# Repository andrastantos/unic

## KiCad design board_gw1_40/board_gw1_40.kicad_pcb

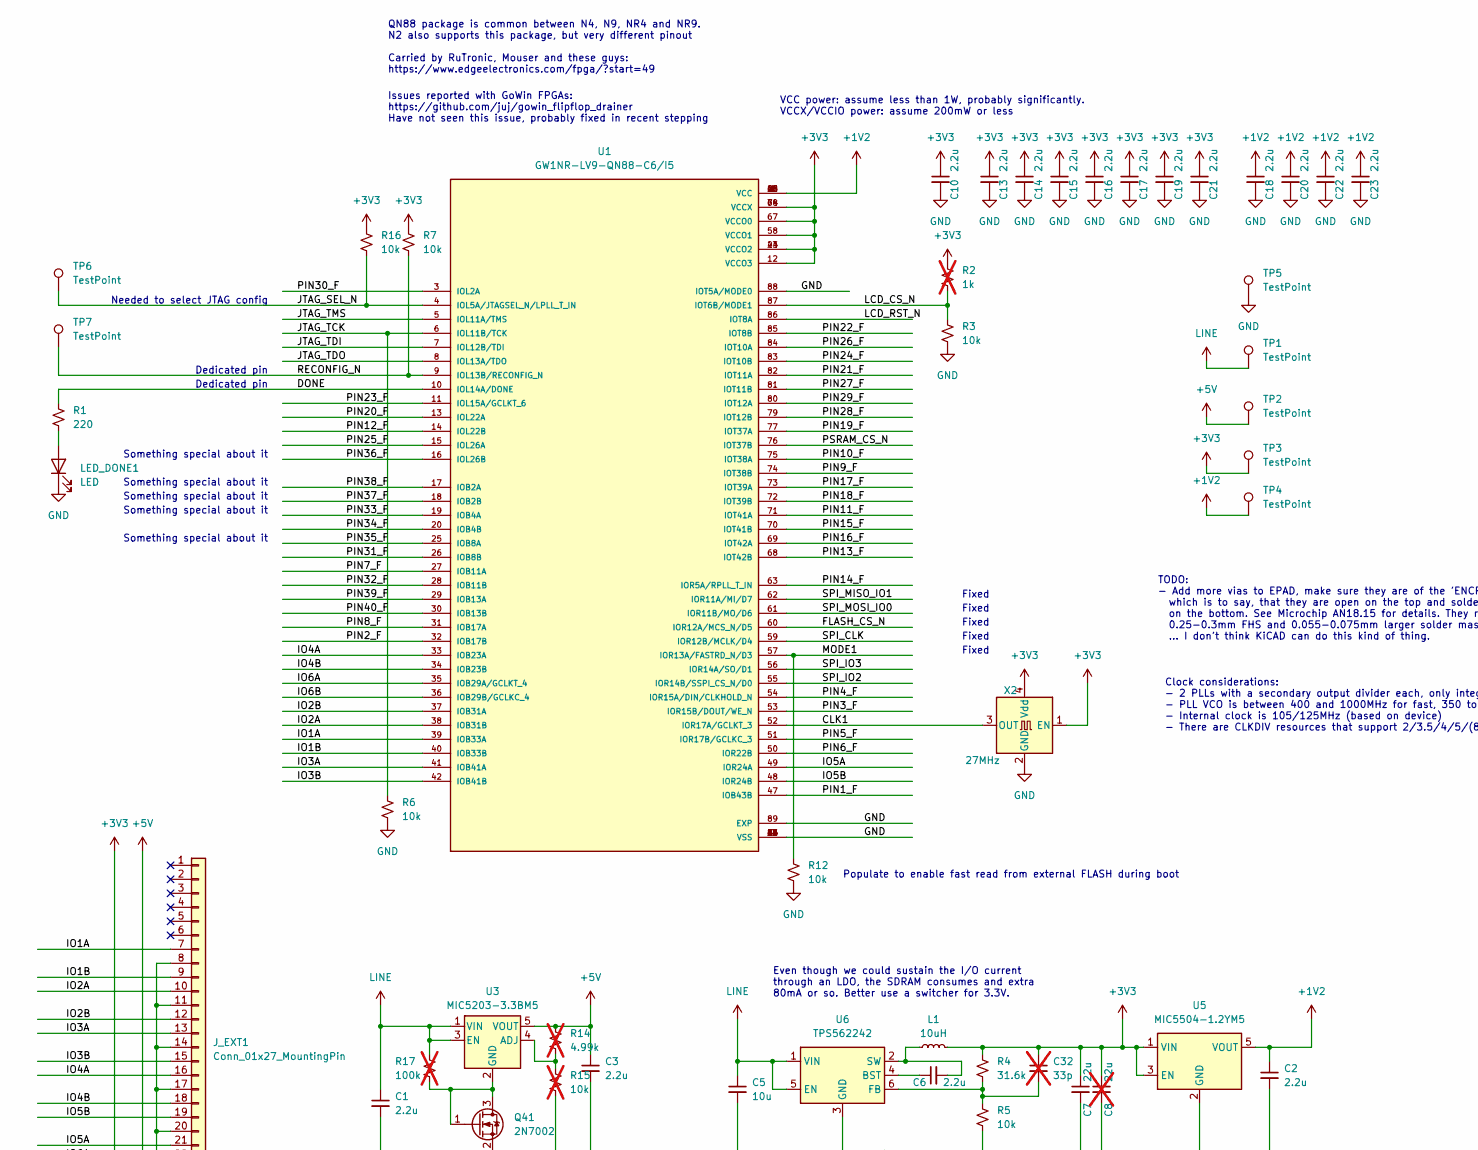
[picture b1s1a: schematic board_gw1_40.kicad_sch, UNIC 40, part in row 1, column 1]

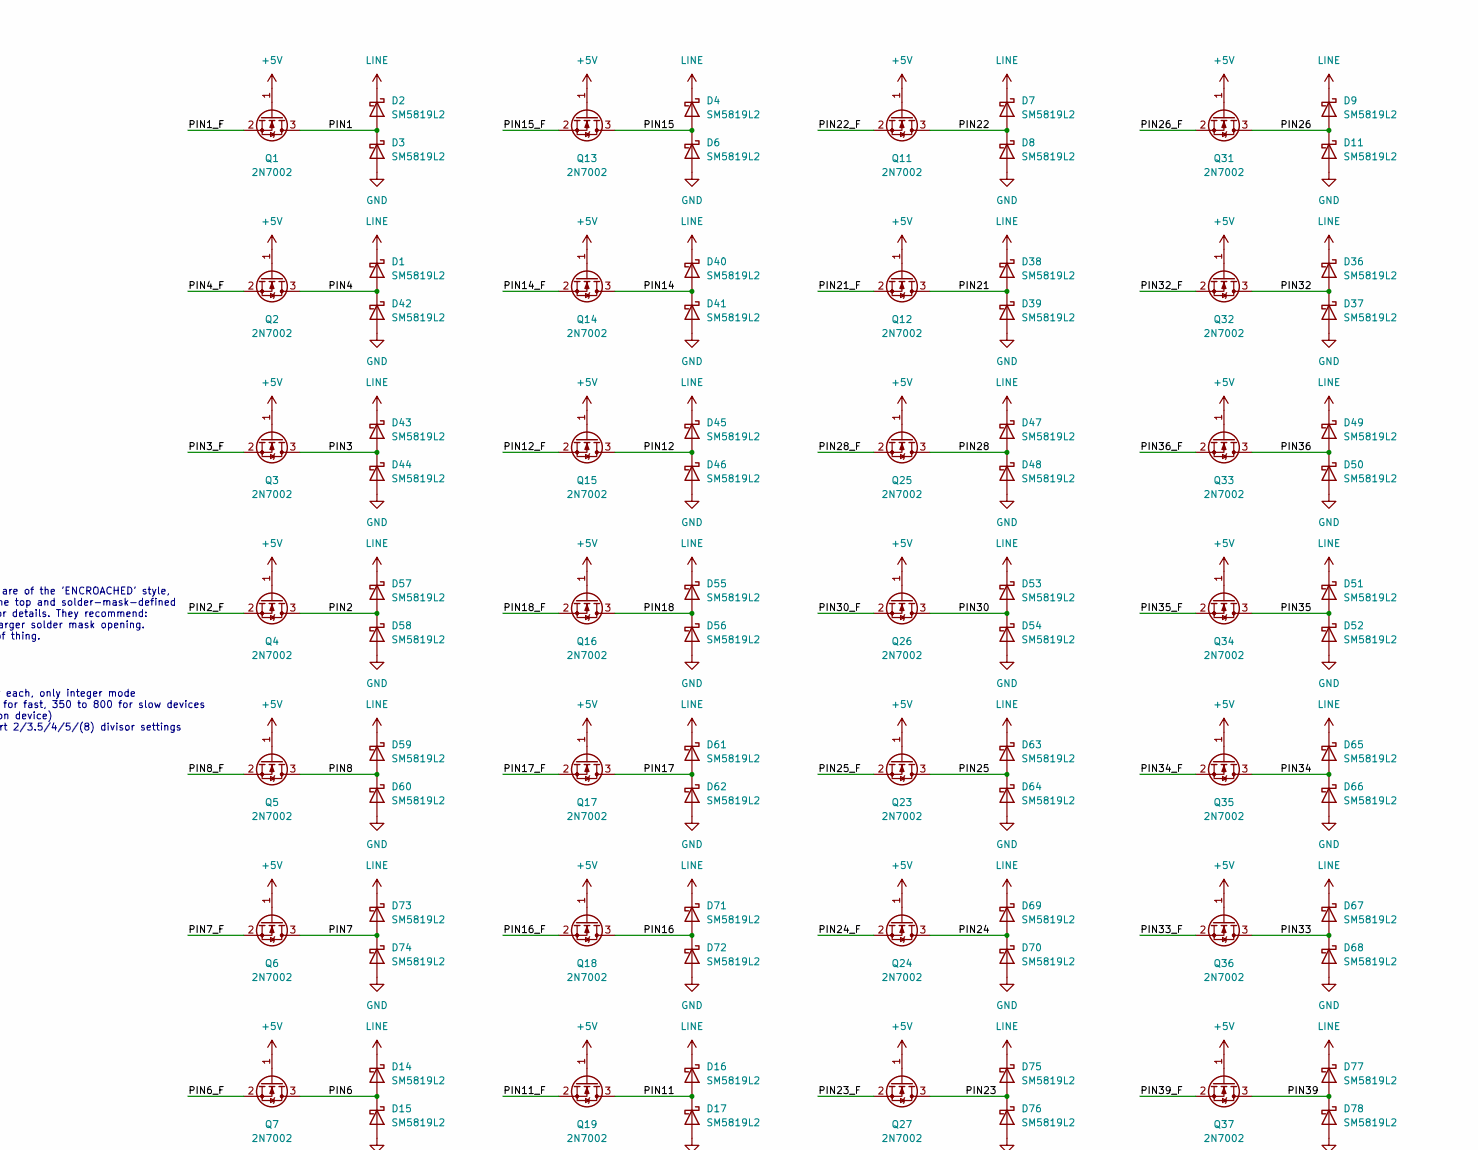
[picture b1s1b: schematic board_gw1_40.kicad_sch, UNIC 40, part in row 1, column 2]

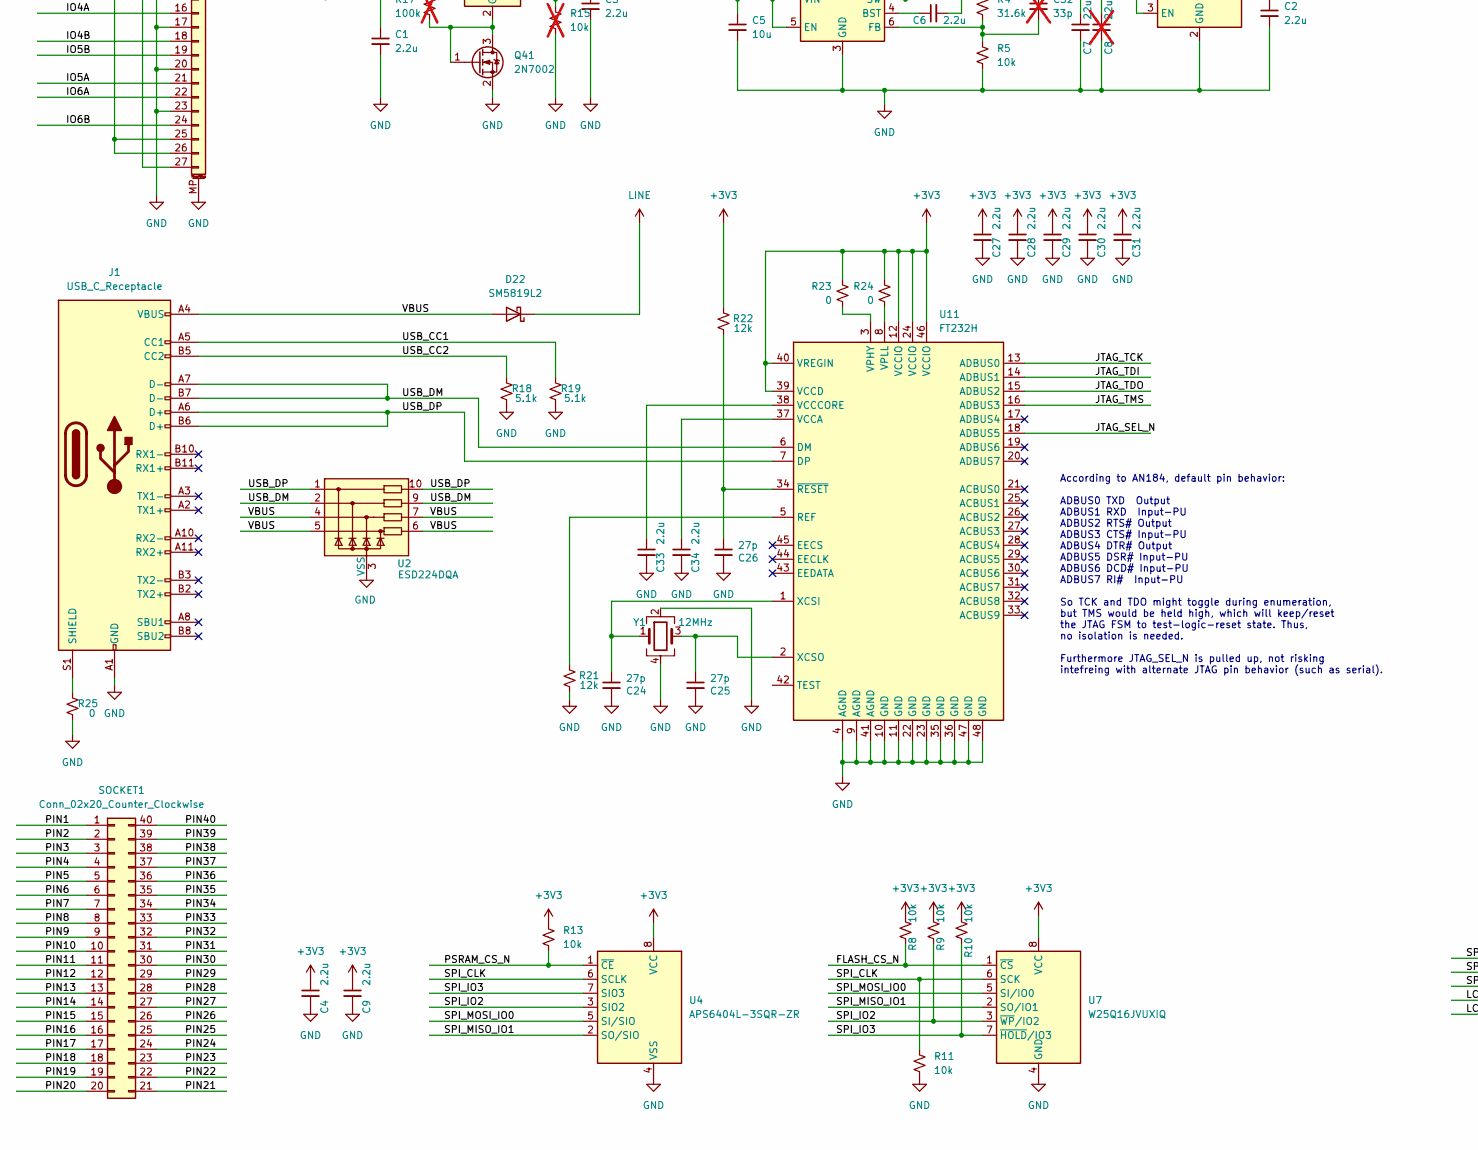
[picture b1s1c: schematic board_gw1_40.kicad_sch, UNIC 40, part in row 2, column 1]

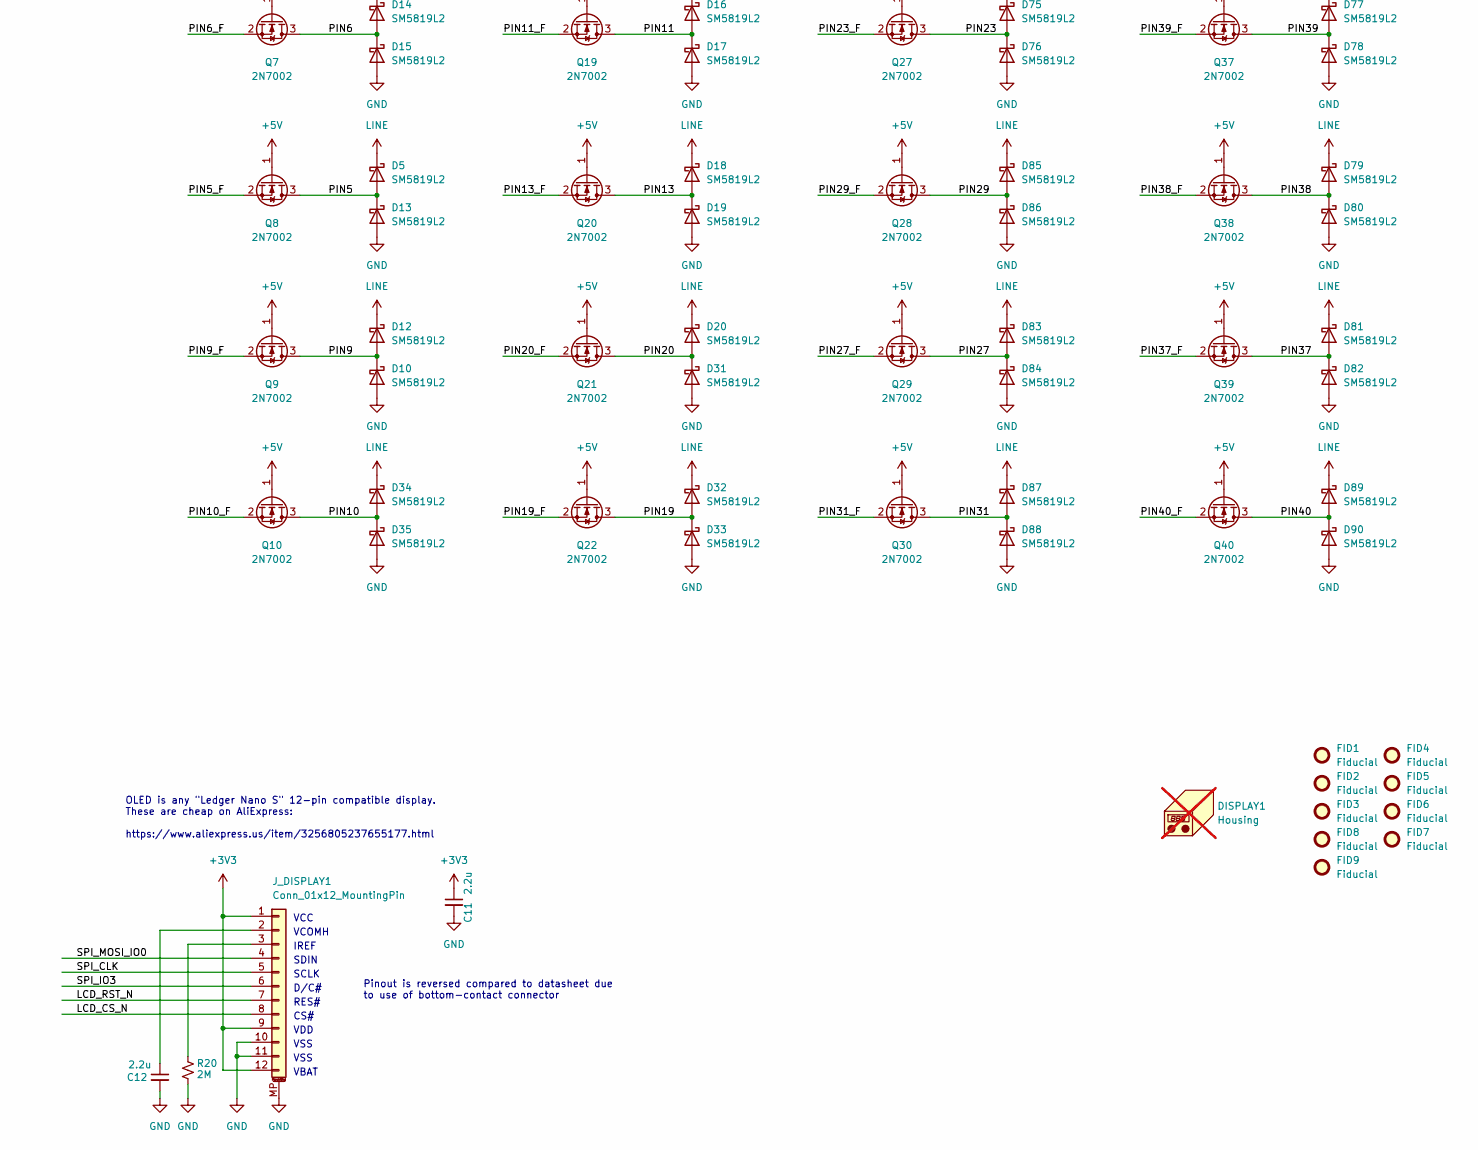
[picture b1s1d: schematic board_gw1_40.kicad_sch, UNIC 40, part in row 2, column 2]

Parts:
C1: 2.2u; C_0402_1005Metric_Pad0.74x0.62mm_HandSolder; mpn CC0402MRX5R6BB225
C2, C3, C4, C6, C9, C10, C11, C12, C13, C14, C15, C16, C17, C18, C19, C20, C21, C22, C23, C27, C28, C29, C30, C31, C33, C34: 2.2u; C_0201_0603Metric; mpn CC0402MRX5R6BB225
C5: 10u; C_0805_2012Metric_Pad1.18x1.45mm_HandSolder; mpn CL21A106KAYNNNG
C7: 22u; C_0805_2012Metric_Pad1.18x1.45mm_HandSolder; mpn CL21A226MQQNNNE
C8: 22u; C_0805_2012Metric_Pad1.18x1.45mm_HandSolder; mpn CL21A226MQQNNNE; not fitted
C24, C25, C26: 27p; C_0201_0603Metric
C32: 33p; C_0201_0603Metric; mpn CC0402MRX5R6BB225; not fitted
D1, D2, D3, D4, D5, D6, D7, D8, D9, D10, D11, D12, D13, D14, D15, D16, D17, D18, D19, D20, D22, D31, D32, D33, D34, D35, D36, D37, D38, D39, D40, D41, D42, D43, D44, D45, D46, D47, D48, D49, D50, D51, D52, D53, D54, D55, D56, D57, D58, D59, D60, D61, D62, D63, D64, D65, D66, D67, D68, D69, D70, D71, D72, D73, D74, D75, D76, D77, D78, D79, D80, D81, D82, D83, D84, D85, D86, D87, D88, D89, D90: SM5819L2; D_SOD-882
DISPLAY1: Housing; CFAL12832C-0091B-W_A; mpn CFAL12832C-0091B-W_A; not fitted
FID1, FID2, FID3, FID4, FID5, FID6, FID7, FID8, FID9: Fiducial; Fiducial_0.5mm_Mask1mm
J1: USB_C_Receptacle; USB_C_Receptacle_GCT_USB4115-03-C
J_DISPLAY1: Conn_01x12_MountingPin; CF4212FH0R0-05-NH; mpn CF31121D0R0-05-NH
J_EXT1: Conn_01x27_MountingPin; Molex_502598-2793_2Rows-23P~0.60mm_Horizontal; mpn 502598-2793
L1: 10uH; L_1008_2520Metric_Pad1.43x2.20mm_HandSolder; mpn UHP 252012BF-100M
LED_DONE1: LED; LED_0402_1005Metric_Pad0.77x0.64mm_HandSolder; mpn CS42C-QL4
Q1, Q2, Q3, Q4, Q5, Q6, Q7, Q8, Q9, Q10, Q11, Q12, Q13, Q14, Q15, Q16, Q17, Q18, Q19, Q20, Q21, Q22, Q23, Q24, Q25, Q26, Q27, Q28, Q29, Q30, Q31, Q32, Q33, Q34, Q35, Q36, Q37, Q38, Q39, Q40, Q41: 2N7002; SOT-883; mpn 2N7002KL3A-TP
R1: 220; R_0201_0603Metric; mpn CR0402-JW-221GLF
R2: 1k; R_0201_0603Metric; mpn CR0402-JW-102GLF; not fitted
R3, R5, R6, R7, R8, R9, R10, R11, R12, R13, R16: 10k; R_0201_0603Metric; mpn CR0402-FX-1002GLF
R4: 31.6k; R_0201_0603Metric; mpn CR0402-FX-3162GLF
R14: 4.99k; R_0201_0603Metric; mpn CR0402-FX-4991GLF; not fitted
R15: 10k; R_0201_0603Metric; mpn CR0402-FX-1002GLF; not fitted
R17: 100k; R_0201_0603Metric; mpn CR0402-FX-1002GLF; not fitted
R18, R19: 5.1k; R_0201_0603Metric
R20: 2M; R_0201_0603Metric
R21, R22: 12k; R_0201_0603Metric
R23, R24, R25: 0; R_0201_0603Metric
SOCKET1: Conn_02x20_Counter_Clockwise; DIP-40_pin_header; mpn BA3760-TUBL-4A-F5
TP1, TP2, TP3, TP4, TP5, TP6, TP7: TestPoint; TestPoint_Pad_D2.0mm
U1: GW1NR-LV9-QN88-C6/I5; QFN40P1000X1000X95-89N; PARTREV UG103-2.3E
U2: ESD224DQA; Diodes_UDFN-10_1.0x2.5mm_P0.5mm; mpn TVU1240R1ADG
U3: MIC5203-3.3BM5; SOT-23-5; mpn MIC5203-3.3YM5-TR
U4: APS6404L-3SQR-ZR; W25Q16JVUXIQ_TR; mpn APS6404L-3SQR-ZR
U5: MIC5504-1.2YM5; SOT-23-5; mpn MIC5504-1.2YM5-TR
U6: TPS562242; SOT-563; mpn TPS562242
U7: W25Q16JVUXIQ; W25Q16JVUXIQ_TR; mpn W25Q16JVUXIQ TR
U11: FT232H; LQFP-48_7x7mm_P0.5mm
X2: 27MHz; Oscillator_SMD_2.5x2.0mm; mpn SG-210STF 27.0000ML5
Y1: 12MHz; Crystal_SMD_2016-4Pin_2.0x1.6mm; mpn E9X250101G03

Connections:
+1V2: C2.1, C18.1, C20.1, C22.1, C23.1, TP4.1, U1.1 (VCC), U1.22 (VCC), U1.45 (VCC), U1.66 (VCC), U5.5 (VOUT)
+3V3: C4.1, C7.1, C8.1, C9.1, C10.1, C11.1, C13.1, C14.1, C15.1, C16.1, C17.1, C19.1, C21.1, C27.1, C28.1, C29.1, C30.1, C31.1, C32.1, J_DISPLAY1.1, J_DISPLAY1.9, J_DISPLAY1.12, J_EXT1.25, J_EXT1.26, L1.2, R2.1, R4.1, R7.1, R8.1, R9.1, R10.1, R13.1, R16.1, R22.2, R23.2, R24.2, TP3.1, U1.12 (VCCO3), U1.23 (VCCO2), U1.44 (VCCO2), U1.58 (VCCO1), U1.64 (VCCX), U1.67 (VCCO0), U1.78 (VCCX), U4.8 (VCC), U5.1 (VIN), U5.3 (EN), U7.8 (VCC), U11.12 (VCCIO), U11.24 (VCCIO), U11.39 (VCCD), U11.40 (VREGIN), U11.46 (VCCIO), X2.1 (EN), X2.4 (Vdd)
+5V: C3.1, J_EXT1.27, Q1.1 (G), Q2.1 (G), Q3.1 (G), Q4.1 (G), Q5.1 (G), Q6.1 (G), Q7.1 (G), Q8.1 (G), Q9.1 (G), Q10.1 (G), Q11.1 (G), Q12.1 (G), Q13.1 (G), Q14.1 (G), Q15.1 (G), Q16.1 (G), Q17.1 (G), Q18.1 (G), Q19.1 (G), Q20.1 (G), Q21.1 (G), Q22.1 (G), Q23.1 (G), Q24.1 (G), Q25.1 (G), Q26.1 (G), Q27.1 (G), Q28.1 (G), Q29.1 (G), Q30.1 (G), Q31.1 (G), Q32.1 (G), Q33.1 (G), Q34.1 (G), Q35.1 (G), Q36.1 (G), Q37.1 (G), Q38.1 (G), Q39.1 (G), Q40.1 (G), R14.1, TP2.1, U3.5 (VOUT)
/CLK1: U1.52 (IOR17A/GCLKT_3), X2.3 (OUT)
/DONE: R1.1, U1.10 (IOL14A/DONE)
/FLASH_CS_N: R8.2, U1.60 (IOR12A/MCS_N/D5), U7.1 (~CS)
/IO1A: J_EXT1.7, U1.39 (IOB33A)
/IO1B: J_EXT1.9, U1.40 (IOB33B)
/IO2A: J_EXT1.10, U1.38 (IOB31B)
/IO2B: J_EXT1.12, U1.37 (IOB31A)
/IO3A: J_EXT1.13, U1.41 (IOB41A)
/IO3B: J_EXT1.15, U1.42 (IOB41B)
/IO4A: J_EXT1.16, U1.33 (IOB23A)
/IO4B: J_EXT1.18, U1.34 (IOB23B)
/IO5A: J_EXT1.21, U1.49 (IOR24A)
/IO5B: J_EXT1.19, U1.48 (IOR24B)
/IO6A: J_EXT1.22, U1.35 (IOB29A/GCLKT_4)
/IO6B: J_EXT1.24, U1.36 (IOB29B/GCLKC_4)
/JTAG_SEL_N: R16.2, TP6.1, U1.4 (IOL5A/JTAGSEL_N/LPLL_T_IN), U11.18 (ADBUS5)
/JTAG_TCK: R6.1, U1.6 (IOL11B/TCK), U11.13 (ADBUS0)
/JTAG_TDI: U1.7 (IOL12B/TDI), U11.14 (ADBUS1)
/JTAG_TDO: U1.8 (IOL13A/TDO), U11.15 (ADBUS2)
/JTAG_TMS: U1.5 (IOL11A/TMS), U11.16 (ADBUS3)
/LCD_CS_N: J_DISPLAY1.8, R2.2, R3.1, U1.87 (IOT6B/MODE1)
/LCD_RST_N: J_DISPLAY1.7, U1.86 (IOT8A)
/MODE1: R12.1, U1.57 (IOR13A/FASTRD_N/D3)
/PIN1: D2.2 (A), D3.1 (K), Q1.3 (D), SOCKET1.1
/PIN1_F: Q1.2 (S), U1.47 (IOB43B)
/PIN2: D57.2 (A), D58.1 (K), Q4.3 (D), SOCKET1.2
/PIN2_F: Q4.2 (S), U1.32 (IOB17B)
/PIN3: D43.2 (A), D44.1 (K), Q3.3 (D), SOCKET1.3
/PIN3_F: Q3.2 (S), U1.53 (IOR15B/DOUT/WE_N)
/PIN4: D1.2 (A), D42.1 (K), Q2.3 (D), SOCKET1.4
/PIN4_F: Q2.2 (S), U1.54 (IOR15A/DIN/CLKHOLD_N)
/PIN5: D5.2 (A), D13.1 (K), Q8.3 (D), SOCKET1.5
/PIN5_F: Q8.2 (S), U1.51 (IOR17B/GCLKC_3)
/PIN6: D14.2 (A), D15.1 (K), Q7.3 (D), SOCKET1.6
/PIN6_F: Q7.2 (S), U1.50 (IOR22B)
/PIN7: D73.2 (A), D74.1 (K), Q6.3 (D), SOCKET1.7
/PIN7_F: Q6.2 (S), U1.27 (IOB11A)
/PIN8: D59.2 (A), D60.1 (K), Q5.3 (D), SOCKET1.8
/PIN8_F: Q5.2 (S), U1.31 (IOB17A)
/PIN9: D10.1 (K), D12.2 (A), Q9.3 (D), SOCKET1.9
/PIN9_F: Q9.2 (S), U1.74 (IOT38B)
/PIN10: D34.2 (A), D35.1 (K), Q10.3 (D), SOCKET1.10
/PIN10_F: Q10.2 (S), U1.75 (IOT38A)
/PIN11: D16.2 (A), D17.1 (K), Q19.3 (D), SOCKET1.11
/PIN11_F: Q19.2 (S), U1.71 (IOT41A)
/PIN12: D45.2 (A), D46.1 (K), Q15.3 (D), SOCKET1.12
/PIN12_F: Q15.2 (S), U1.14 (IOL22B)
/PIN13: D18.2 (A), D19.1 (K), Q20.3 (D), SOCKET1.13
/PIN13_F: Q20.2 (S), U1.68 (IOT42B)
/PIN14: D40.2 (A), D41.1 (K), Q14.3 (D), SOCKET1.14
/PIN14_F: Q14.2 (S), U1.63 (IOR5A/RPLL_T_IN)
/PIN15: D4.2 (A), D6.1 (K), Q13.3 (D), SOCKET1.15
/PIN15_F: Q13.2 (S), U1.70 (IOT41B)
/PIN16: D71.2 (A), D72.1 (K), Q18.3 (D), SOCKET1.16
/PIN16_F: Q18.2 (S), U1.69 (IOT42A)
/PIN17: D61.2 (A), D62.1 (K), Q17.3 (D), SOCKET1.17
/PIN17_F: Q17.2 (S), U1.73 (IOT39A)
/PIN18: D55.2 (A), D56.1 (K), Q16.3 (D), SOCKET1.18
/PIN18_F: Q16.2 (S), U1.72 (IOT39B)
/PIN19: D32.2 (A), D33.1 (K), Q22.3 (D), SOCKET1.19
/PIN19_F: Q22.2 (S), U1.77 (IOT37A)
/PIN20: D20.2 (A), D31.1 (K), Q21.3 (D), SOCKET1.20
/PIN20_F: Q21.2 (S), U1.13 (IOL22A)
/PIN21: D38.2 (A), D39.1 (K), Q12.3 (D), SOCKET1.21
/PIN21_F: Q12.2 (S), U1.82 (IOT11A)
/PIN22: D7.2 (A), D8.1 (K), Q11.3 (D), SOCKET1.22
/PIN22_F: Q11.2 (S), U1.85 (IOT8B)
/PIN23: D75.2 (A), D76.1 (K), Q27.3 (D), SOCKET1.23
/PIN23_F: Q27.2 (S), U1.11 (IOL15A/GCLKT_6)
/PIN24: D69.2 (A), D70.1 (K), Q24.3 (D), SOCKET1.24
/PIN24_F: Q24.2 (S), U1.83 (IOT10B)
/PIN25: D63.2 (A), D64.1 (K), Q23.3 (D), SOCKET1.25
/PIN25_F: Q23.2 (S), U1.15 (IOL26A)
/PIN26: D9.2 (A), D11.1 (K), Q31.3 (D), SOCKET1.26
/PIN26_F: Q31.2 (S), U1.84 (IOT10A)
/PIN27: D83.2 (A), D84.1 (K), Q29.3 (D), SOCKET1.27
/PIN27_F: Q29.2 (S), U1.81 (IOT11B)
/PIN28: D47.2 (A), D48.1 (K), Q25.3 (D), SOCKET1.28
/PIN28_F: Q25.2 (S), U1.79 (IOT12B)
/PIN29: D85.2 (A), D86.1 (K), Q28.3 (D), SOCKET1.29
/PIN29_F: Q28.2 (S), U1.80 (IOT12A)
/PIN30: D53.2 (A), D54.1 (K), Q26.3 (D), SOCKET1.30
/PIN30_F: Q26.2 (S), U1.3 (IOL2A)
/PIN31: D87.2 (A), D88.1 (K), Q30.3 (D), SOCKET1.31
/PIN31_F: Q30.2 (S), U1.26 (IOB8B)
/PIN32: D36.2 (A), D37.1 (K), Q32.3 (D), SOCKET1.32
/PIN32_F: Q32.2 (S), U1.28 (IOB11B)
/PIN33: D67.2 (A), D68.1 (K), Q36.3 (D), SOCKET1.33
/PIN33_F: Q36.2 (S), U1.19 (IOB4A)
/PIN34: D65.2 (A), D66.1 (K), Q35.3 (D), SOCKET1.34
/PIN34_F: Q35.2 (S), U1.20 (IOB4B)
/PIN35: D51.2 (A), D52.1 (K), Q34.3 (D), SOCKET1.35
/PIN35_F: Q34.2 (S), U1.25 (IOB8A)
/PIN36: D49.2 (A), D50.1 (K), Q33.3 (D), SOCKET1.36
/PIN36_F: Q33.2 (S), U1.16 (IOL26B)
/PIN37: D81.2 (A), D82.1 (K), Q39.3 (D), SOCKET1.37
/PIN37_F: Q39.2 (S), U1.18 (IOB2B)
/PIN38: D79.2 (A), D80.1 (K), Q38.3 (D), SOCKET1.38
/PIN38_F: Q38.2 (S), U1.17 (IOB2A)
/PIN39: D77.2 (A), D78.1 (K), Q37.3 (D), SOCKET1.39
/PIN39_F: Q37.2 (S), U1.29 (IOB13A)
/PIN40: D89.2 (A), D90.1 (K), Q40.3 (D), SOCKET1.40
/PIN40_F: Q40.2 (S), U1.30 (IOB13B)
/PSRAM_CS_N: R13.2, U1.76 (IOT37B), U4.1 (~CE)
/RECONFIG_N: R7.2, TP7.1, U1.9 (IOL13B/RECONFIG_N)
/SPI_CLK: J_DISPLAY1.5, R11.1, U1.59 (IOR12B/MCLK/D4), U4.6 (SCLK), U7.6 (SCK)
/SPI_IO2: R9.2, U1.55 (IOR14B/SSPI_CS_N/D0), U4.3 (SIO2), U7.3 (~WP/IO2)
/SPI_IO3: J_DISPLAY1.6, R10.2, U1.56 (IOR14A/SO/D1), U4.7 (SIO3), U7.7 (~HOLD/IO3)
/SPI_MISO_IO1: U1.62 (IOR11A/MI/D7), U4.2 (SO/SIO), U7.2 (SO/IO1)
/SPI_MOSI_IO0: J_DISPLAY1.4, U1.61 (IOR11B/MO/D6), U4.5 (SI/SIO), U7.5 (SI/IO0)
/USB_CC1: J1.A5 (CC1), R19.2
/USB_CC2: J1.B5 (CC2), R18.2
/USB_DM: J1.A7 (D-), J1.B7 (D-), U2.2, U2.9, U11.6 (DM)
/USB_DP: J1.A6 (D+), J1.B6 (D+), U2.1, U2.10, U11.7 (DP)
/VBUS: D22.2 (A), J1.A4 (VBUS), J1.A9 (VBUS), J1.B4 (VBUS), J1.B9 (VBUS), U2.4, U2.5, U2.6, U2.7
GND: C1.2, C2.2, C3.2, C4.2, C5.2, C7.2, C8.2, C9.2, C10.2, C11.2, C12.2, C13.2, C14.2, C15.2, C16.2, C17.2, C18.2, C19.2, C20.2, C21.2, C22.2, C23.2, C24.2, C25.2, C26.2, C27.2, C28.2, C29.2, C30.2, C31.2, C33.2, C34.2, D3.2 (A), D6.2 (A), D8.2 (A), D10.2 (A), D11.2 (A), D13.2 (A), D15.2 (A), D17.2 (A), D19.2 (A), D31.2 (A), D33.2 (A), D35.2 (A), D37.2 (A), D39.2 (A), D41.2 (A), D42.2 (A), D44.2 (A), D46.2 (A), D48.2 (A), D50.2 (A), D52.2 (A), D54.2 (A), D56.2 (A), D58.2 (A), D60.2 (A), D62.2 (A), D64.2 (A), D66.2 (A), D68.2 (A), D70.2 (A), D72.2 (A), D74.2 (A), D76.2 (A), D78.2 (A), D80.2 (A), D82.2 (A), D84.2 (A), D86.2 (A), D88.2 (A), D90.2 (A), J1.A1 (GND), J1.A12 (GND), J1.B1 (GND), J1.B12 (GND), J_DISPLAY1.10, J_DISPLAY1.11, J_DISPLAY1.MP (MountPin), J_EXT1.8, J_EXT1.11, J_EXT1.14, J_EXT1.17, J_EXT1.20, J_EXT1.23, J_EXT1.MP (MountPin), LED_DONE1.1 (K), Q41.2 (S), R3.2, R5.2, R6.2, R11.2, R12.2, R15.2, R18.1, R19.1, R20.2, R21.1, R25.1, TP5.1, U1.2 (VSS), U1.21 (VSS), U1.24 (VSS), U1.43 (VSS), U1.46 (VSS), U1.65 (VSS), U1.88 (IOT5A/MODE0), U1.89 (EXP), U2.3 (VSS), U2.8 (VSS), U4.4 (VSS), U5.2 (GND), U6.3 (GND), U7.4 (GND), U11.4 (AGND), U11.9 (AGND), U11.10 (GND), U11.11 (GND), U11.22 (GND), U11.23 (GND), U11.35 (GND), U11.36 (GND), U11.41 (AGND), U11.47 (GND), U11.48 (GND), X2.2 (GND), Y1.2, Y1.4
LINE: C1.1, C5.1, D1.1 (K), D2.1 (K), D4.1 (K), D5.1 (K), D7.1 (K), D9.1 (K), D12.1 (K), D14.1 (K), D16.1 (K), D18.1 (K), D20.1 (K), D22.1 (K), D32.1 (K), D34.1 (K), D36.1 (K), D38.1 (K), D40.1 (K), D43.1 (K), D45.1 (K), D47.1 (K), D49.1 (K), D51.1 (K), D53.1 (K), D55.1 (K), D57.1 (K), D59.1 (K), D61.1 (K), D63.1 (K), D65.1 (K), D67.1 (K), D69.1 (K), D71.1 (K), D73.1 (K), D75.1 (K), D77.1 (K), D79.1 (K), D81.1 (K), D83.1 (K), D85.1 (K), D87.1 (K), D89.1 (K), R17.1, TP1.1, U3.1 (VIN), U3.3 (EN), U6.1 (VIN), U6.5 (EN)
unnamed: J1.S1 (SHIELD), R25.2
unnamed: C12.1, J_DISPLAY1.2
unnamed: J_DISPLAY1.3, R20.1
unnamed: LED_DONE1.2 (A), R1.2
unnamed: Q41.1 (G), Q41.3 (D), R17.2, U3.2 (GND)
unnamed: R14.2, R15.1, U3.4 (ADJ)
unnamed: C6.1, U6.4 (BST)
unnamed: C32.2, R4.2, R5.1, U6.6 (FB)
unnamed: C6.2, L1.1, U6.2 (SW)
unnamed: R21.2, U11.5 (REF)
unnamed: C34.1, U11.37 (VCCA)
unnamed: C33.1, U11.38 (VCCCORE)
unnamed: R23.1, U11.3 (VPHY)
unnamed: R24.1, U11.8 (VPLL)
unnamed: C24.1, U11.1 (XCSI), Y1.1
unnamed: C25.1, U11.2 (XCSO), Y1.3
unnamed: C26.1, R22.1, U11.34 (~RESET)

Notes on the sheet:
Issues reported with GoWin FPGAs: https://github.com/juj/gowin_flipflop_drainer Have not seen this issue, probably fixed in recent stepping
Populate to enable fast read from external FLASH during boot
Pinout is reversed compared to datasheet due to use of bottom-contact connector
Fixed
Something special about it
CS#
TODO: - Add more vias to EPAD, make sure they are of the 'ENCROACHED' style, which is to say, that they are open on the top and solder-mask-defined on the bottom. See Microchip AN18.15 for details. They recommend: 0.25-0.3mm FHS and 0.055-0.075mm larger solder mask opening. ... I don't think KiCAD 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
VCC
VSS
VCC power: assume less than 1W, probably significantly. VCCX/VCCIO power: assume 200mW or less
OLED is any "Ledger Nano S" 12-pin compatible display. These are cheap on AliExpress: https://www.aliexpress.us/item/3256805237655177.html
SCLK
Clock considerations: - 2 PLLs with a secondary output divider each, only integer mode - PLL VCO is between 400 and 1000MHz for fast, 350 to 800 for slow devices - Internal clock is 105/125MHz (based on device) - There are CLKDIV resources that support 2/3.5/4/5/(8) divisor settings
Even though we could sustain the I/O current through an LDO, the SDRAM consumes and extra 80mA or so. Better use a switcher for 3.3V.
Dedicated pin
VDD
RES#
SDIN
Needed to select JTAG config
VCOMH
IREF
QN88 package is common between N4, N9, NR4 and NR9. N2 also supports this package, but very different pinout Carried by RuTronic, Mouser and these guys: https://www.edgeelectronics.com/fpga/?start=49
According to AN184, default pin behavior: ADBUS0 TXD Output ADBUS1 RXD Input-PU ADBUS2 RTS# Output ADBUS3 CTS# Input-PU ADBUS4 DTR# Output ADBUS5 DSR# Input-PU ADBUS6 DCD# Input-PU ADBUS7 RI# Input-PU So TCK and TDO might toggle during enumeration, but TMS would be held high, which will keep/reset 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
D/C#
VBAT

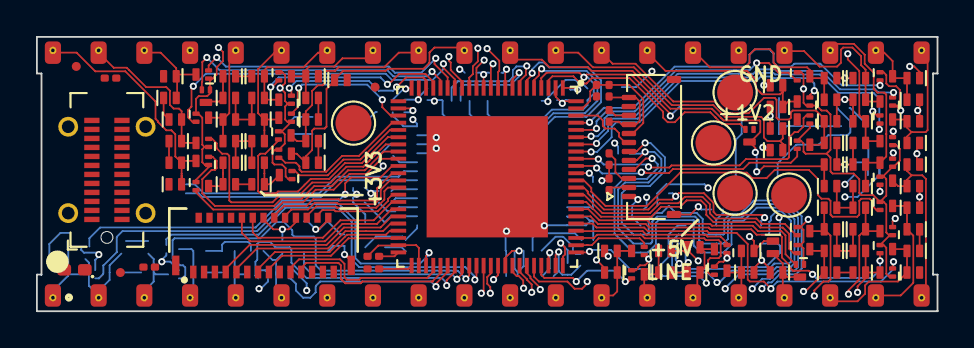
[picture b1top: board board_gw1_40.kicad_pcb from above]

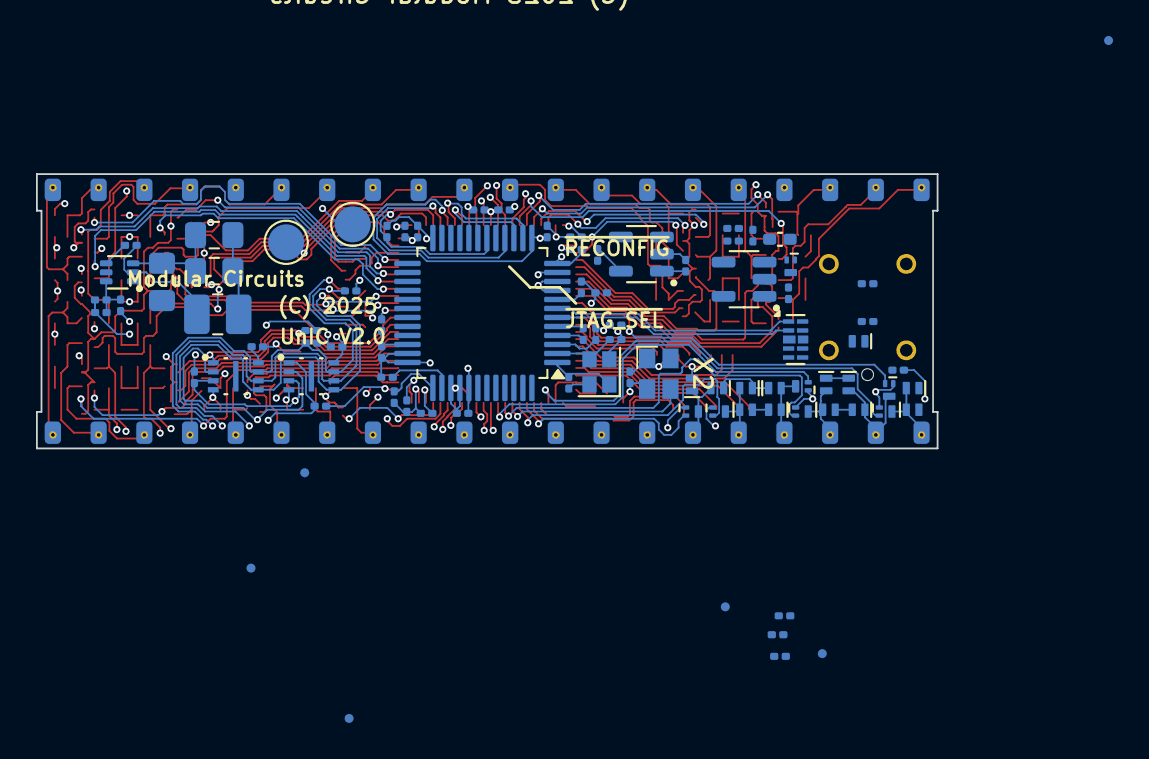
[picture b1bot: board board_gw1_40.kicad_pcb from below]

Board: 4 copper layers, 50.0 x 15.2 mm, 214 parts (88 on the bottom side), 137 nets.

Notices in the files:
board_gw1_24/board_gw1_24.kicad_pcb:
(C) 2025 Modular Circuits
board_gw1_40/board_gw1_40.kicad_pcb:
(C) 2025
board_rp/unic_rp.kicad_pcb:
(C) 2024 Modular Circuits
shadow_tracer/shadow_tracer.kicad_pcb:
(C) 2024 Andras Tantos &
